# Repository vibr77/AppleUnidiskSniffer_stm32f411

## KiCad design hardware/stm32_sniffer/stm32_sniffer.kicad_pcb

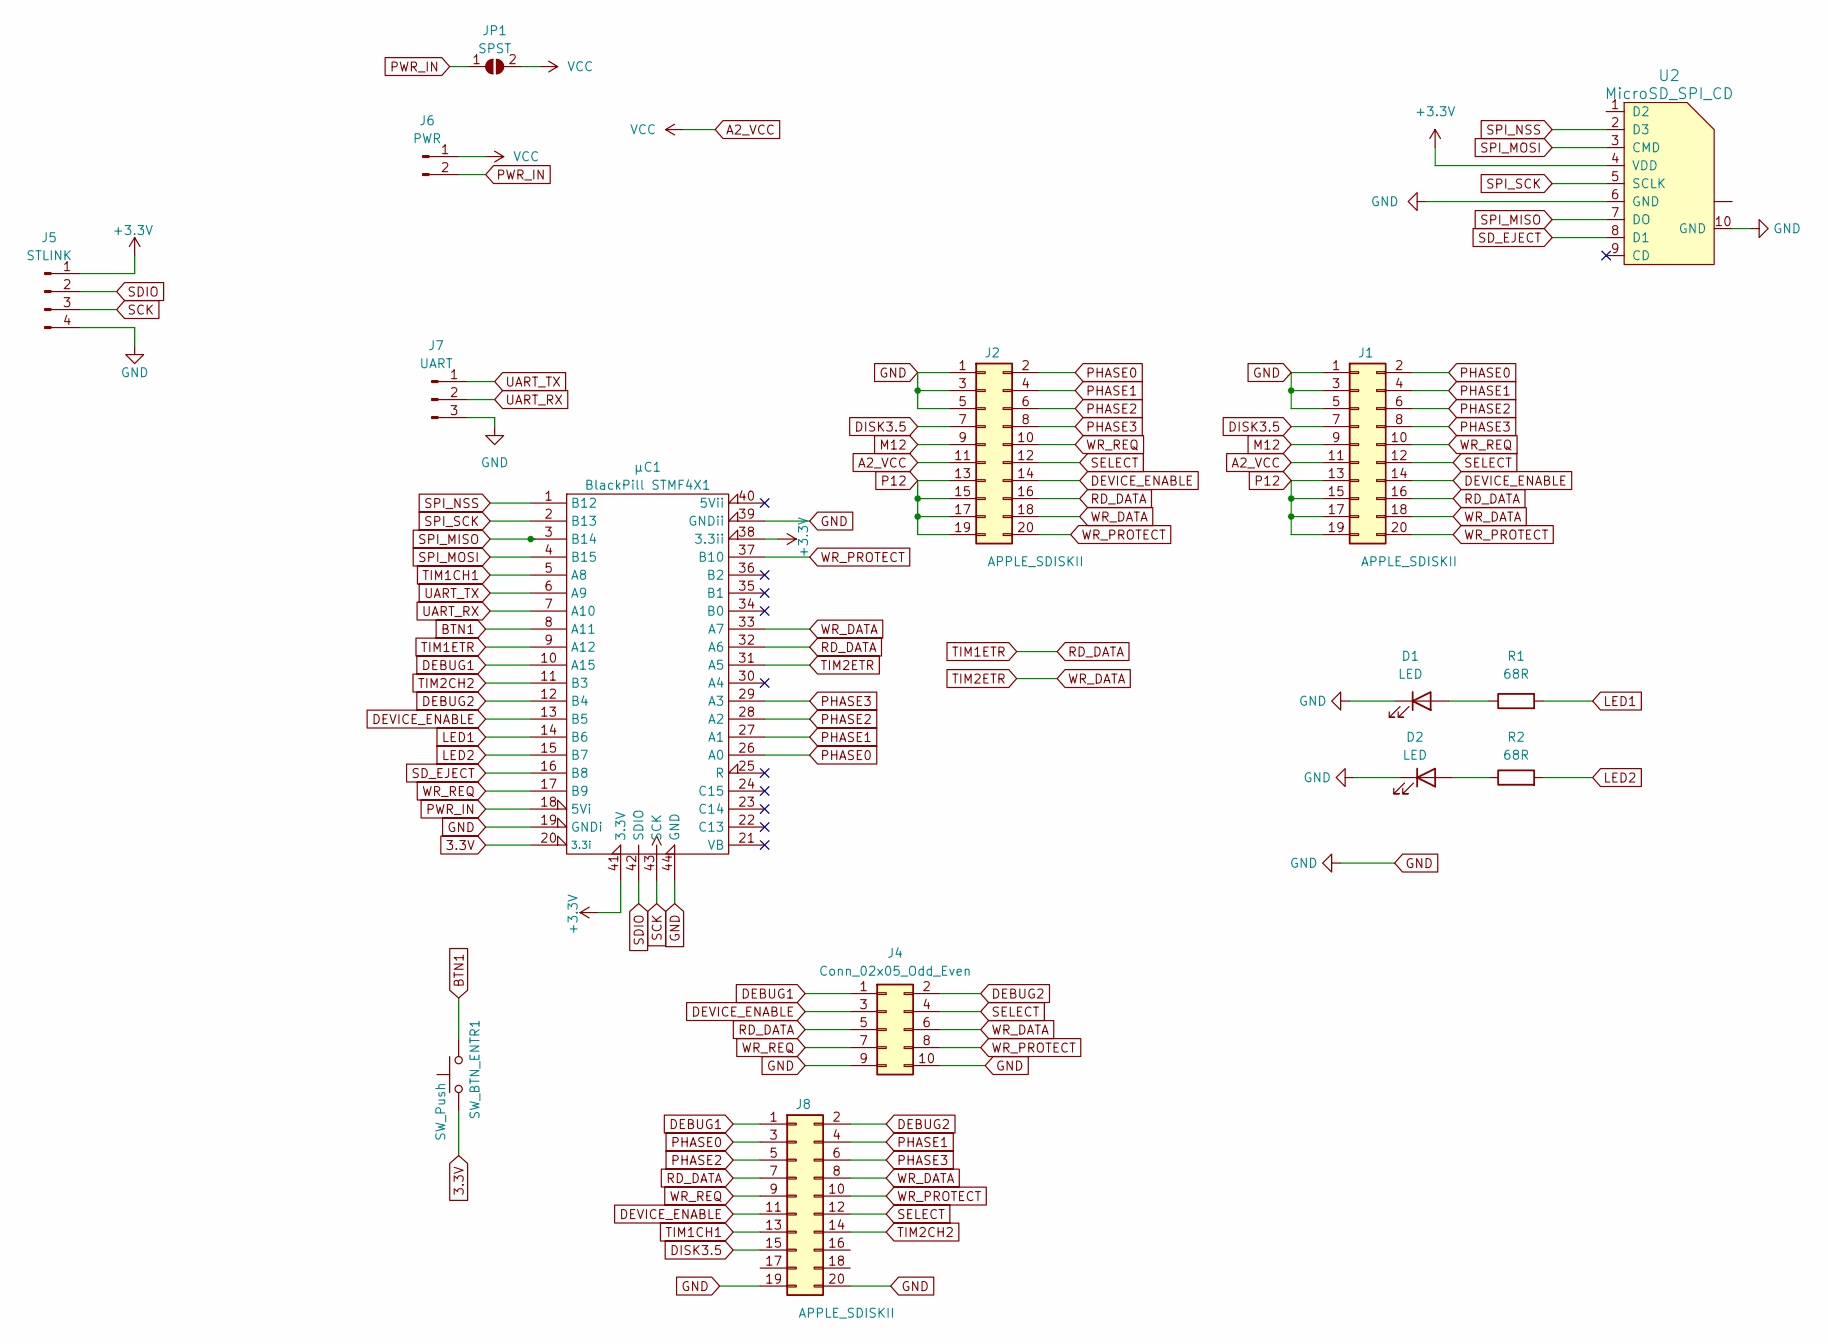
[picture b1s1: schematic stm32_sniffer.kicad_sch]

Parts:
D1, D2: LED; LED_D5.0mm
J1, J2: APPLE_SDISKII; IDC-Header_2x10_P2.54mm_Vertical
J4: Conn_02x05_Odd_Even; IDC-Header_2x05_P2.54mm_Vertical
J5: STLINK; PinHeader_1x04_P2.54mm_Vertical
J6: PWR; PinHeader_1x02_P2.54mm_Vertical
J7: UART; PinHeader_1x03_P2.54mm_Vertical
J8: APPLE_SDISKII; PinHeader_2x10_P2.54mm_Vertical
JP1: SPST; SolderJumper-2_P1.3mm_Open_RoundedPad1.0x1.5mm
R1, R2: 68R; R_Axial_DIN0207_L6.3mm_D2.5mm_P7.62mm_Horizontal
SW_BTN_ENTR1: SW_Push; SW_PUSH_6mm
U2: MicroSD_SPI_CD; GCT-MEM2055-00-190-01-A
μC1: BlackPill STMF4X1; Mini_F4X1_STM32_VIB

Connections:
3.3V: SW_BTN_ENTR1.1, μC1.20 (3.3i); also elsewhere on the board
+3.3V: J5.1, U2.4 (VDD), μC1.38 (3.3ii), μC1.41 (3.3V)
A2_VCC: J1.11, J2.11, J6.1, JP1.2 (B)
BTN1: SW_BTN_ENTR1.2, μC1.8 (A11); also elsewhere on the board
DEBUG1: J4.1, J8.1, μC1.10 (A15)
DEBUG2: J4.2, J8.2, μC1.12 (B4)
DEVICE_ENABLE: J1.14, J2.14, J4.3, J8.11, μC1.13 (B5)
DISK3.5: J1.7, J2.7, J8.15
GND: D1.1 (K), D2.1 (K), J1.1, J1.3, J1.5, J2.1, J2.3, J2.5, J4.9, J4.10, J5.4, J7.3, J8.19, J8.20, U2.6 (GND), U2.10 (GND), μC1.19 (GNDi), μC1.39 (GNDii), μC1.44 (GND)
LED1: R1.2, μC1.14 (B6)
LED2: R2.2, μC1.15 (B7)
M12: J1.9, J2.9
unnamed: D1.2 (A), R1.1
unnamed: D2.2 (A), R2.1
P12: J1.13, J1.15, J1.17, J1.19, J2.13, J2.15, J2.17, J2.19
PHASE0: J1.2, J2.2, J8.3, μC1.26 (A0)
PHASE1: J1.4, J2.4, J8.4, μC1.27 (A1)
PHASE2: J1.6, J2.6, J8.5, μC1.28 (A2)
PHASE3: J1.8, J2.8, J8.6, μC1.29 (A3)
PWR_IN: J6.2, JP1.1 (A), μC1.18 (5Vi)
RD_DATA: J1.16, J2.16, J4.5, J8.7, μC1.9 (A12), μC1.32 (A6)
SCK: J5.3, μC1.43 (SCK)
SDIO: J5.2, μC1.42 (SDIO)
SD_EJECT: U2.8 (D1), μC1.16 (B8)
SELECT: J1.12, J2.12, J4.4, J8.12
SPI_MISO: U2.7 (DO), μC1.3 (B14)
SPI_MOSI: U2.3 (CMD), μC1.4 (B15)
SPI_NSS: U2.2 (D3), μC1.1 (B12)
SPI_SCK: U2.5 (SCLK), μC1.2 (B13)
TIM1CH1: J8.13, μC1.5 (A8)
TIM2CH2: J8.14, μC1.11 (B3)
TIM2ETR: J1.18, J2.18, J4.6, J8.8, μC1.31 (A5), μC1.33 (A7)
UART_RX: J7.2, μC1.7 (A10)
UART_TX: J7.1, μC1.6 (A9)
WR_PROTECT: J1.20, J2.20, J4.8, J8.10, μC1.37 (B10)
WR_REQ: J1.10, J2.10, J4.7, J8.9, μC1.17 (B9)

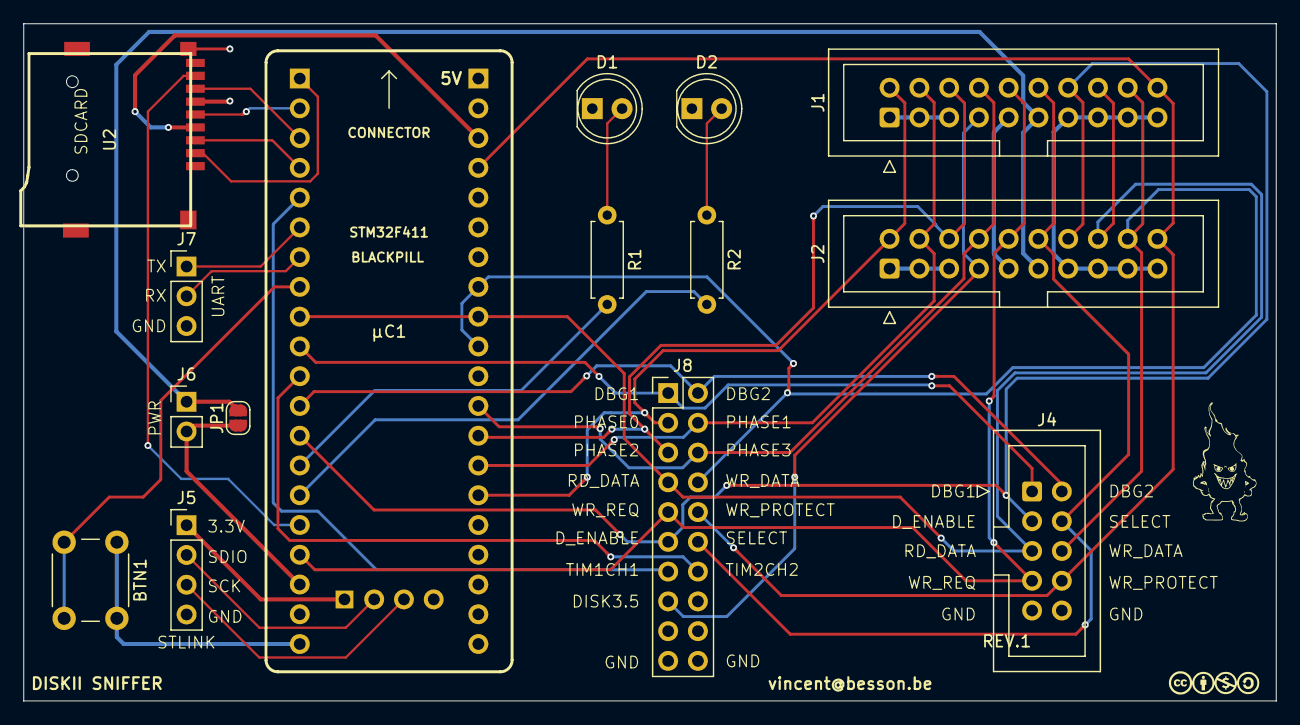
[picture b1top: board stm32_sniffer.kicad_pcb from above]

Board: 2 copper layers, 106.9 x 57.8 mm, 16 parts (0 on the bottom side), 36 nets.

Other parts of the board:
 : LOGO
BTN1: SW_Push; SW_PUSH_6mm

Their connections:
3.3V: BTN1.1; also elsewhere on the board
BTN1: BTN1.2; also elsewhere on the board

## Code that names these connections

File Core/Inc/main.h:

/* USER CODE BEGIN Header */
/**
  ******************************************************************************
  * @file           : main.h
  * @brief          : Header for main.c file.
  *                   This file contains the common defines of the application.
  ******************************************************************************
  * @attention
  *
  * Copyright (c) 2025 STMicroelectronics.
  * All rights reserved.
  *
  * This software is licensed under terms that can be found in the LICENSE file
  * in the root directory of this software component.
  * If no LICENSE file comes with this software, it is provided AS-IS.
  *
  ******************************************************************************
  */
/* USER CODE END Header */

/* Define to prevent recursive inclusion -------------------------------------*/
#ifndef __MAIN_H
#define __MAIN_H

#ifdef __cplusplus
extern "C" {
#endif

/* Includes ------------------------------------------------------------------*/
#include "stm32f4xx_hal.h"

/* Private includes ----------------------------------------------------------*/
/* USER CODE BEGIN Includes */

/* USER CODE END Includes */

/* Exported types ------------------------------------------------------------*/
/* USER CODE BEGIN ET */
#ifdef __GNUC__
#define PUTCHAR_PROTOTYPE int __io_putchar(int ch)
#else
#define PUTCHAR_PROTOTYPE int fputc(int ch, FILE *f)
#endif
/* USER CODE END ET */

/* Exported constants --------------------------------------------------------*/
/* USER CODE BEGIN EC */

/* USER CODE END EC */

/* Exported macro ------------------------------------------------------------*/
/* USER CODE BEGIN EM */

/* USER CODE END EM */

void HAL_TIM_MspPostInit(TIM_HandleTypeDef *htim);

/* Exported functions prototypes ---------------------------------------------*/
void Error_Handler(void);

/* USER CODE BEGIN EFP */

/* USER CODE END EFP */

/* Private defines -----------------------------------------------------------*/
#define PHASE0_Pin GPIO_PIN_0
#define PHASE0_GPIO_Port GPIOA
#define PHASE0_EXTI_IRQn EXTI0_IRQn
#define PHASE1_Pin GPIO_PIN_1
#define PHASE1_GPIO_Port GPIOA
#define PHASE1_EXTI_IRQn EXTI1_IRQn
#define PHASE2_Pin GPIO_PIN_2
#define PHASE2_GPIO_Port GPIOA
#define PHASE2_EXTI_IRQn EXTI2_IRQn
#define PHASE3_Pin GPIO_PIN_3
#define PHASE3_GPIO_Port GPIOA
#define PHASE3_EXTI_IRQn EXTI3_IRQn
#define RD_DATA_Pin GPIO_PIN_6
#define RD_DATA_GPIO_Port GPIOA
#define WR_DATA_Pin GPIO_PIN_7
#define WR_DATA_GPIO_Port GPIOA
#define WR_PROTECT_Pin GPIO_PIN_10
#define WR_PROTECT_GPIO_Port GPIOB
#define WR_PROTECT_EXTI_IRQn EXTI15_10_IRQn
#define DEBUG1_Pin GPIO_PIN_15
#define DEBUG1_GPIO_Port GPIOA
#define DEBUG2_Pin GPIO_PIN_3
#define DEBUG2_GPIO_Port GPIOB
#define DEVICE_ENABLE_Pin GPIO_PIN_5
#define DEVICE_ENABLE_GPIO_Port GPIOB
#define DEVICE_ENABLE_EXTI_IRQn EXTI9_5_IRQn
#define WR_REQ_Pin GPIO_PIN_9
#define WR_REQ_GPIO_Port GPIOB
#define WR_REQ_EXTI_IRQn EXTI9_5_IRQn

/* USER CODE BEGIN Private defines */
void SmartPortDeviceEnableIRQ();
void SmartPortWrReqIRQ();
void SmartPortPhaseIRQ();
void SmartPortWpAckIRQ();

/* USER CODE END Private defines */

#ifdef __cplusplus
}
#endif

#endif /* __MAIN_H */

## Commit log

2025-03-09 v0.1
2025-03-09 0.11
2025-03-10 hardware pcb
